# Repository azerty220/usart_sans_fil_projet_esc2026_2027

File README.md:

# Projet de Transmission UART Sans Fil
Projet Système réalisé en troisième année spécialité Electronique et Systèmes de Communication à l'ENSEA : 

> Mise en place d'une communication sans fil USART avec un drône

## Cahier des charges

L'objectif de ce projet est de concevoir une chaîne de transmission/réception RF à partir de composants existants. Cet émetteur-récepteur est destiné à la communication avec un drone. Il y a donc une contrainte de place sur au moins une des versions du système.

Contraintes générales :

    Portée du système : 10m
    Durée du projet : 40h
    Budget : 250€

Paramètres de l'USART fourni : 

    Débit : 115 200 baud
    8 bits de données
    1 bit de parité (pair)
    1 bit de stop

## Choix de la fréquence porteuse et de la modulation
Nous avons choisi une porteuse à **868MHz**, ainsi que la modulation **ASK**,    
- Notre choix s'est porté sur la modulation ASK afin d'obtenir une portée nettement supérieure. De plus, nous avons pris en compte l'expérience d'un groupe ayant réalisé ce même projet en 2025 avec la modulation BPSK : leur choix avait entraîné de lourdes difficultés, notamment au niveau de la démodulation et de la récupération de la porteuse en phase. Cette dernière nécessitait en effet une PLL sans erreur de phase, alors qu'une PLL est initialement conçue pour minimiser les erreurs de fréquence.    
- En ce qui concerne la fréquence, nous avons choisi de réutiliser les composants des années précédentes afin de réduire les coûts. De plus, opter pour la bande des 2,4 GHz très proche de la band Wi-Fi nous aurait exposé à de nombreux signaux parasites, qui auraient été difficiles à filtrer.

## Vue d'ensemble du système émission/réception
Voici une description de notre système. Celui-ci s'organise autour d'une chaîne d'émission (composée du modulateur ASK, du PA et du filtrage) et d'une chaîne de réception (composée du filtrage, du LNA et du démodulateur ASK). Pour permettre l'utilisation d'une seule antenne dans les deux modes, les deux chaînes sont reliées par un Switch RF qui permet de passer d'un mode à l'autre. L'ensemble est piloté par un microcontrôleur µC et la porteuse elle est générée par l'oscillateur local :    

Dans un premier temps, nous avons découpé le système par fonctions : chaque binôme s'est vu assigner une tâche spécifique et devait réaliser un premier PCB (2 couches) dédié. Dans un second temps, une fois les tests validés, un PCB unique à 4 couches a été conçu pour regrouper l'ensemble du système.

# Description de la chaîne d'émission
Le rôle principal de la chaîne d'émission, consiste à traiter les données numériques reçues par liaison UART, à générer une porteuse radiofréquence à 868 MHz (stabilisée par un oscillateur local à boucle à verrouillage de phase (PLL)), puis à appliquer une modulation d'amplitude de type ASK (Amplitude Shift Keying). Le signal ainsi modulé traverse ensuite un étage de filtrage avant d'être acheminé vers l'antenne.
    <br>Le développement de cette chaîne d'émission a été structuré autour de plusieurs objectifs clés :
        <br> 1- Garantir l'intégrité et la fiabilité de la transmission des données numériques via l'interface UART.
        <br> 2- Produire un signal porteur RF stable, propre et paramétrable.
        <br> 3- Exécuter une modulation ASK fidèle aux trames de données à transmettre.
        <br> 4- Filtrer efficacement le signal radiofréquence pour respecter les normes en vigueur avant son émission par l'antenne.
## Bloc génération de la porteuse et modulation ASK
Cette partie décrit le fonctionnement des premiers bloc (Modulateur ASK et Oscillateur Local) de la chaîne détaillée précédemment, la génération de la porteuse sera réalisée par le synthétiseur de fréquence à boucle à verrouillage de phase (PLL) l’ADF4350, afin d’avoir une référence de fréquence, ce dernier sera relié à l’oscillateur ECS-TXD-20CSMV-AC-260-AY-TR et enfin pour réaliser la modulation ASK, nous utiliserons un switch RF, l’ADG918BCPZ.

### 1- interface Nucléo/PCB RF
La communication entre la carte microcontrôleur (Nucleo STM32) et le PCB RF est assurée par plusieurs connecteurs dédiés :

    • Connecteur d'interface SPI (J2) : regroupant les signaux de configuration SCK (horloge de communication), DATA (données de configuration), LE (validation du registre sélectionné) et CE (activation du composant), ainsi que la masse GND, permettant le paramétrage du synthétiseur de fréquence.
    • Connecteur de commande (J3) : acheminant le signal de commande UART_RX issu du microcontrôleur vers le modulateur ASK.
    • Connecteur d'alimentation (J6) : fournissant les tensions +3.3V, +2V5 (utiles pour alimenter l’ADF4350, ADG918 et l’oscillateur) et la référence de masse GND à la carte.
### 2- Génération de la porteuse

###3- Modulation ASK
<br>-> SMA vers le PCB amplificateur de puissance et filtrage
<br> Vue d'ensemble du PCB

## Bloc amplificateur de puissance et filtrage
Callum et Elise

# Switch RF et antenne
Commutation entre les 2 modes -> Johan

# Description de la chaîne de réception
choix des composants modules par module
## Bloc filtrage et LNA
Julie L et Rafik
## Bloc Démodulateur
Awa

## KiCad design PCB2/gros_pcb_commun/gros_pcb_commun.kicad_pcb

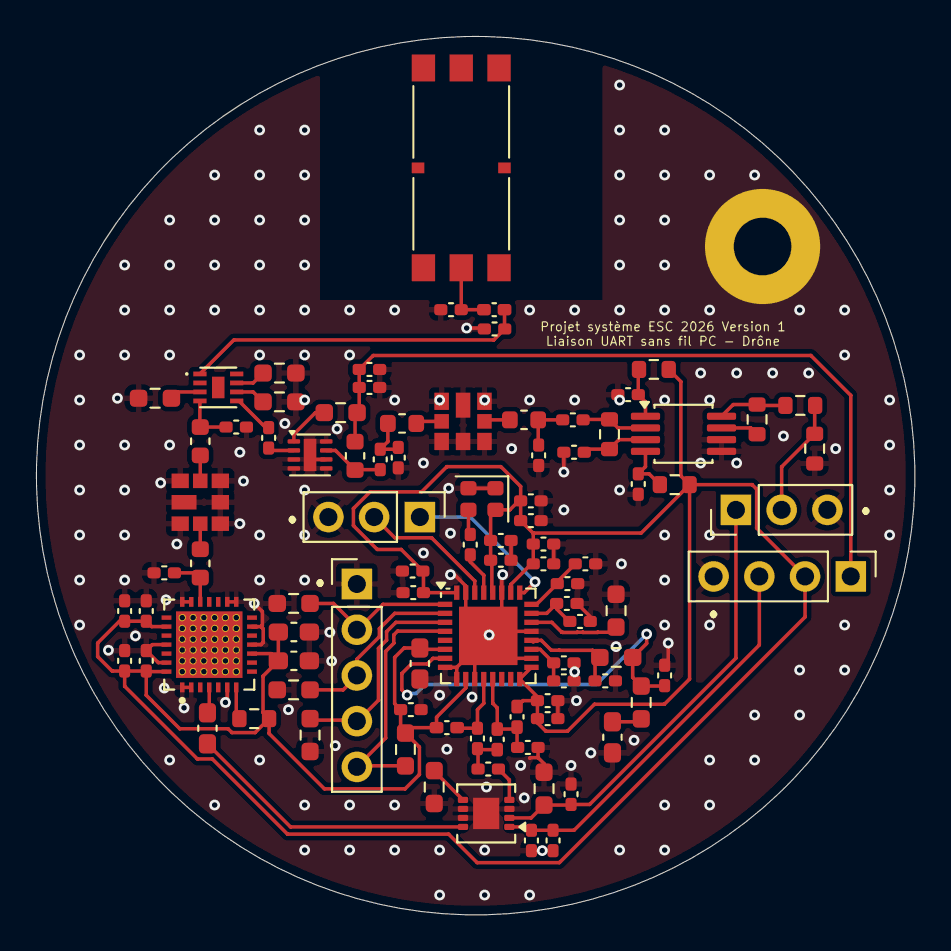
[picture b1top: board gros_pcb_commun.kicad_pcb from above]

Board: 2 copper layers, 48.8 x 48.8 mm, 93 parts (0 on the bottom side), 52 nets.

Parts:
AE1: Antenna; AE_Wurth_WE-MCA_7488910092
C1, C3, C5, C7, C9: 100 nF; C_0402_1005Metric_Pad0.74x0.62mm_HandSolder
C2, C4, C6, C10, C13, C15, C17, C27: 10 pF; C_0402_1005Metric_Pad0.74x0.62mm_HandSolder
C8: 10 pF; C_0603_1608Metric_Pad1.08x0.95mm_HandSolder
C11: 1 uF; C_0402_1005Metric_Pad0.74x0.62mm_HandSolder
C12, C14, C16, C18, C28, C42, C43: 0.1 uF; C_0402_1005Metric_Pad0.74x0.62mm_HandSolder
C19: 1 nF; C_0402_1005Metric_Pad0.74x0.62mm_HandSolder
C20, C21: 4 nF; C_0402_1005Metric_Pad0.74x0.62mm_HandSolder
C22: 120 pF; C_0402_1005Metric_Pad0.74x0.62mm_HandSolder
C23: 42.3 nF; C_0402_1005Metric_Pad0.74x0.62mm_HandSolder
C24: 575 nF; C_0603_1608Metric_Pad1.08x0.95mm_HandSolder
C25: 19.3 nF; C_0402_1005Metric_Pad0.74x0.62mm_HandSolder
C26: 100 pF; C_0402_1005Metric_Pad0.74x0.62mm_HandSolder
C29, C32, C35, C36: 0.1u; C_0402_1005Metric_Pad0.74x0.62mm_HandSolder
C30: 2.7p; C_0402_1005Metric_Pad0.74x0.62mm_HandSolder
C31: 33p; C_0603_1608Metric_Pad1.08x0.95mm_HandSolder
C33, C37: 10u; C_0603_1608Metric_Pad1.08x0.95mm_HandSolder
C34: 3.5p; C_0402_1005Metric_Pad0.74x0.62mm_HandSolder
C38: 3.9pF; C_0402_1005Metric_Pad0.74x0.62mm_HandSolder
C39: 3.3pF; C_0402_1005Metric_Pad0.74x0.62mm_HandSolder
C40, C41: 680 pF; C_0402_1005Metric_Pad0.74x0.62mm_HandSolder
C44: 47pF; C_0402_1005Metric_Pad0.74x0.62mm_HandSolder
C45: 4.7pF; C_0402_1005Metric_Pad0.74x0.62mm_HandSolder
C46: 100nF; C_0402_1005Metric_Pad0.74x0.62mm_HandSolder
C47: 100pF; C_0402_1005Metric_Pad0.74x0.62mm_HandSolder
C48: 2,7pF; C_0402_1005Metric_Pad0.74x0.62mm_HandSolder
C49: 3,5pF; C_0402_1005Metric_Pad0.74x0.62mm_HandSolder
FL1: SF2425E
H3: MountingHole_Pad; MountingHole_3.2mm_M3_Pad
J1: Conn_01x03_Pin; PinHeader_1x03_P2.54mm_Vertical
J2: Conn_01x04_Pin; PinHeader_1x04_P2.54mm_Vertical
J3: Conn_01x05; PinHeader_1x05_P2.54mm_Vertical
J4: Conn_01x03; PinHeader_1x03_P2.54mm_Vertical
L1: 68 nH; L_0402_1005Metric_Pad0.77x0.64mm_HandSolder
L2, L3: 18 nH; L_0402_1005Metric_Pad0.77x0.64mm_HandSolder
L4, L5: 24n; L_0603_1608Metric
L6: 12nH; L_0402_1005Metric_Pad0.77x0.64mm_HandSolder
L7, L8, L9: 22nH; L_0603_1608Metric
R1, R2, R3, R5, R8, R11, R12, R13: 10k; R_0603_1608Metric_Pad0.98x0.95mm_HandSolder
R4: 5.1 k; R_0603_1608Metric_Pad0.98x0.95mm_HandSolder
R6: 59.7; R_0603_1608Metric_Pad0.98x0.95mm_HandSolder
R7: 122; R_0603_1608Metric_Pad0.98x0.95mm_HandSolder
R9: 50; R_0603_1608Metric_Pad0.98x0.95mm_HandSolder
R10: 5k1; R_0603_1608Metric
R14, R17: 10; R_0603_1608Metric
R15: 53,6; R_0603_1608Metric
R16: 0; R_0603_1608Metric
R18: 910; R_0603_1608Metric_Pad0.98x0.95mm_HandSolder
RL1: 1M; R_0603_1608Metric
Rprot1: 500; R_0603_1608Metric
SF1: SF2425E
U1: ADF4350; LFCSP-32-1EP_5x5mm_P0.5mm_EP3.25x3.25mm
U2: ADG918BCPZ; LFCSP-8-1EP_3x3mm_P0.5mm_EP1.45x1.74mm
U3: SKY66185-11; IC_SKY66185-11
U4: SON50P200X200X60-9N160X90
U5: AD8313xRM; MSOP-8_3x3mm_P0.65mm
U6: GRF2070; DFN-8-2x2mm_P0.7mm
Y1: ECS-TXO-20CSMV-AC-260-AY-TR; Oscillator_SMD_SiT_PQFN-4Pin_2.0x1.6mm

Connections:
+2V5: C27.1, C28.1, J2.3, U2.1 (VDD)
+5V: C46.1, C47.1, J2.1, L7.1, R18.1
A+: C20.1, L2.2, U1.12 (RF_OUT_A+)
A-: C21.1, L1.2, L3.2, U1.13 (RF_OUT_A-)
AVDD: C1.2, C2.2, C3.2, C4.2, C5.2, C6.2, C7.2, C8.2, C9.2, C10.2, C11.1, C12.1, C29.2, C32.2, C33.2, C35.1, C36.1, C37.1, J2.2, L1.1, L2.1, R2.1, R10.1, R14.1, R17.2, U1.6 (Vp), U1.10 (AVDD), U1.16 (VVCO), U1.17 (VVCO), U1.26 (PDB_RF), U1.28 (DVDD), U1.32 (SDVDD), U3.10 (VBIAS), U3.23 (VCC3), U3.28 (VCC1), Y1.4 (VDD)
CE: J3.5, R2.2, U1.4 (CE)
DATA: J3.3, R3.1, U1.2 (DATA)
FiltreIN: C30.1, L4.1, U3.19 (RFOUT)
GND: C1.1, C2.1, C3.1, C4.1, C5.1, C6.1, C7.1, C8.1, C9.1, C10.1, C11.2, C12.2, C13.2, C14.2, C15.2, C16.2, C17.2, C18.2, C21.2, C23.2, C24.2, C25.2, C26.2, C27.2, C28.2, C29.1, C30.2, C32.1, C33.1, C34.2, C35.2, C36.2, C37.2, C38.2, C39.2, C41.1, C42.2, C43.1, C46.2, C47.2, C48.2, C49.1, FL1.1 (IN_GND), FL1.3 (GND), FL1.4 (GND), FL1.5 (OUT_GND), FL1.7 (GND), FL1.8 (GND), H3.1, J1.3, J2.4, J3.1, J4.3, R1.2, R3.2, R4.1, R5.2, R8.2, R9.2, R11.2, R12.2, R13.2, RL1.1, SF1.1 (IN_GND), SF1.3 (GND), SF1.4 (GND), SF1.5 (OUT_GND), SF1.7 (GND), SF1.8 (GND), U1.8 (CPGND), U1.9 (AGND), U1.11 (AGNDVCO), U1.18 (AGNDVCO), U1.21 (AGNDVCO), U1.27 (DGND), U1.31 (SDGND), U1.33 (EP), U2.3 (GND), U2.6 (GND), U2.7 (GND), U2.9 (GND), U3.1 (GND), U3.2 (GND), U3.6 (GND), U3.11 (GND), U3.13 (GND), U3.15 (GND), U3.16 (GND), U3.20 (GND), U3.21 (GND), U3.25 (GND), U3.27 (GND), U5.5 (PWDN), U5.6 (COMM), U6.3 (GND), U6.4 (GND), U6.5 (GND), U6.6 (GND), U6.8 (GND), U6.9 (EP), Y1.1 (GROUND_1), Y1.2 (GROUND_2)
LE: J3.4, R1.1, U1.3 (LE)
unnamed: AE1.2 (A), C39.1, L6.2
unnamed: C20.2, C22.1, L3.1
unnamed: C24.1, R6.2
unnamed: C42.1, R14.2, U5.1 (VPOS)
unnamed: C43.2, R17.1, U5.4 (VPOS)
unnamed: C45.2, C48.1, L8.1
unnamed: FL1.2 (IN), L8.2
unnamed: FL1.6 (OUT), L9.1
unnamed: J4.1, U1.25 (LD)
unnamed: J4.2, U1.30 (MUXOUT)
unnamed: L4.2, SF1.2 (IN)
unnamed: L5.1, SF1.6 (OUT)
unnamed: C23.1, R6.1, R7.2, U1.7 (CPout)
unnamed: R4.2, U1.22 (RSET)
unnamed: C25.1, R7.1, U1.20 (VTUNE)
unnamed: R9.1, U2.5 (RF2)
unnamed: C31.2, U3.4 (RFIN)
unnamed: R10.2, U3.7 (~VEN)
unnamed: C38.1, L6.1, U4.1 (RFC)
unnamed: R11.1, U4.3 (V1)
unnamed: R12.1, U4.6 (V2)
unnamed: R13.1, U4.7 (V3)
unnamed: C40.2, R15.1, U5.2 (INHI)
unnamed: C41.2, R15.2, U5.3 (INLO)
unnamed: R16.1, Rprot1.1, U5.8 (VOUT)
unnamed: R16.2, U5.7 (VSET)
unnamed: C44.2, U6.2 (RF_IN)
unnamed: C45.1, L7.2, U6.7 (RF_OUT/VDD)
unnamed: R18.2, U6.1 (VENABLE)
unnamed: C19.1, Y1.3 (OUTPUT)
Porteuse_RFC: C22.2, U2.4 (RFC)
REFIN: C19.2, U1.29 (REFIN)
SCK: J3.2, R5.1, U1.1 (CLK)
TEMP: C13.1, C14.1, U1.19 (TEMP)
VCOM: C15.1, C16.1, U1.23 (VCOM)
VREF: C17.1, C18.1, U1.24 (VREF)
sig0: C26.1, J1.1, R8.1, U2.2 (CTRL)
sig1: C31.1, U2.8 (RF1)
sig2: C34.1, L5.2, U4.4 (RF1)
sig3: C44.1, U4.5 (RF2)
sig4: C40.1, C49.2, L9.2
sig5: J1.2, RL1.2, Rprot1.2

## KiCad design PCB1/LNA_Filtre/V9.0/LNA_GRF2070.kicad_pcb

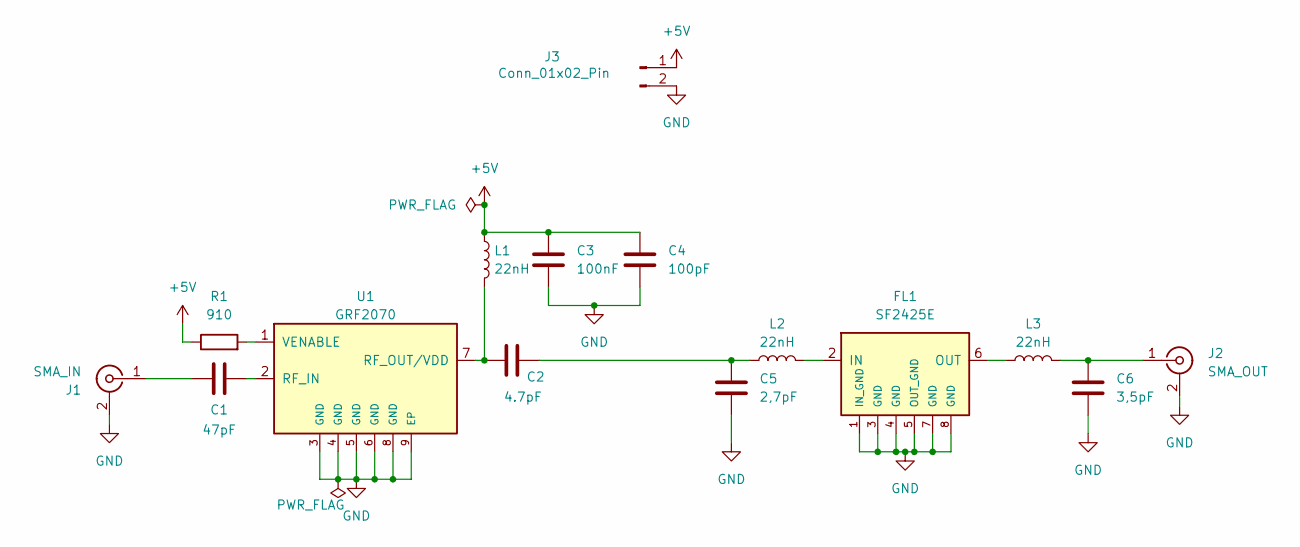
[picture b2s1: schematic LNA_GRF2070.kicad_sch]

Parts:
C1: 47pF; C_0603_1608Metric
C2: 4.7pF; C_0603_1608Metric
C3: 100nF; C_0603_1608Metric
C4: 100pF; C_0603_1608Metric
C5: 2,7pF; C_0603_1608Metric
C6: 3,5pF; C_0603_1608Metric
FL1: SF2425E
J1: SMA_IN; SMA_Samtec_SMA-J-P-H-ST-EM1_EdgeMount
J2: SMA_OUT; SMA_Samtec_SMA-J-P-H-ST-EM1_EdgeMount
J3: Conn_01x02_Pin; PinHeader_1x02_P2.54mm_Vertical
L1, L2, L3: 22nH; L_0603_1608Metric
R1: 910; R_0603_1608Metric_Pad0.98x0.95mm_HandSolder
U1: GRF2070; WDFN-8-1EP_2x2.2mm_P0.5mm_EP0.80x0.54

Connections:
+5V: C3.1, C4.1, J3.1, L1.1, R1.1
GND: C3.2, C4.2, C5.2, C6.1, FL1.1 (IN_GND), FL1.3 (GND), FL1.4 (GND), FL1.5 (OUT_GND), FL1.7 (GND), FL1.8 (GND), J1.2 (Ext), J2.2 (Ext), J3.2, U1.3 (GND), U1.4 (GND), U1.5 (GND), U1.6 (GND), U1.8 (GND), U1.9 (EP)
unnamed: C2.2, C5.1, L2.1
unnamed: FL1.2 (IN), L2.2
unnamed: FL1.6 (OUT), L3.1
unnamed: C1.1, J1.1 (In)
unnamed: C6.2, J2.1 (In), L3.2
unnamed: C1.2, U1.2 (RF_IN)
unnamed: C2.1, L1.2, U1.7 (RF_OUT/VDD)
unnamed: R1.2, U1.1 (VENABLE)

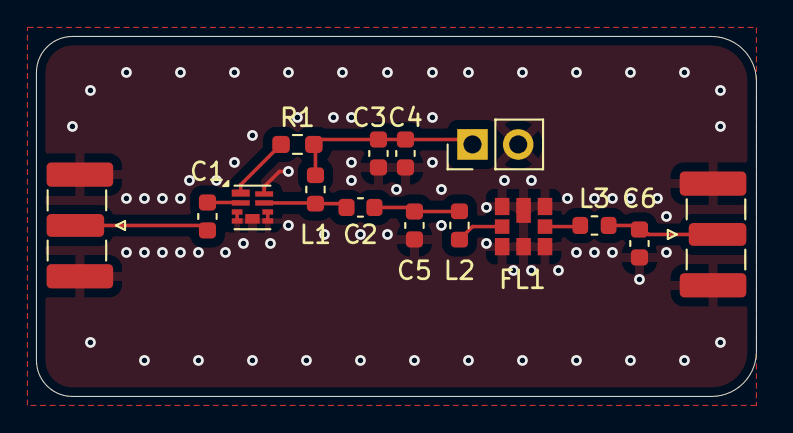
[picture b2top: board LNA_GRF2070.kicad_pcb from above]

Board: 2 copper layers, 40.0 x 20.0 mm, 15 parts (0 on the bottom side), 10 nets.

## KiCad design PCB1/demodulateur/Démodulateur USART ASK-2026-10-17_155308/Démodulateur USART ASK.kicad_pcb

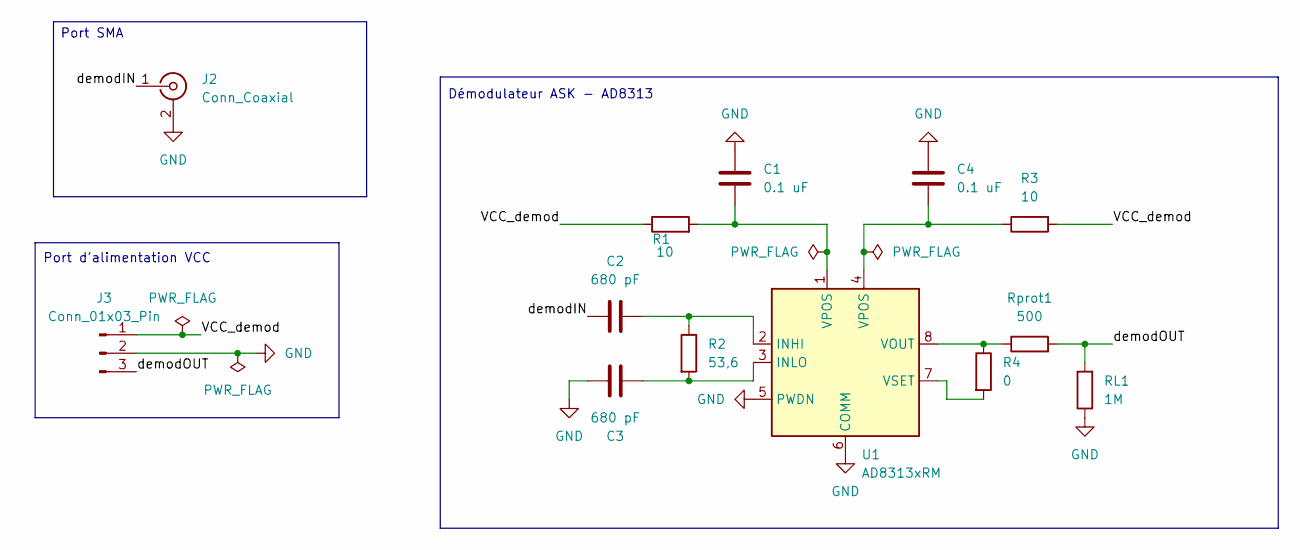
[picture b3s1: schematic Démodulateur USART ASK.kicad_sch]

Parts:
C1, C4: 0.1 uF; C_0603_1608Metric
C2, C3: 680 pF; C_0603_1608Metric
J2: Conn_Coaxial; SMA_Samtec_SMA-J-P-H-ST-EM1_EdgeMount
J3: Conn_01x03_Pin; PinHeader_1x03_P2.54mm_Vertical
R1, R3: 10; R_0603_1608Metric
R2: 53,6; R_0603_1608Metric
R4: 0; R_0603_1608Metric
RL1: 1M; R_0603_1608Metric
Rprot1: 500; R_0603_1608Metric
U1: AD8313xRM; MSOP-8_3x3mm_P0.65mm

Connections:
/VCC_demod: J3.1, R1.1, R3.2
/demodIN: C2.1, J2.1 (In)
/demodOUT: J3.3, RL1.2, Rprot1.2
GND: C1.2, C3.1, C4.1, J2.2 (Ext), J3.2, RL1.1, U1.5 (PWDN), U1.6 (COMM)
unnamed: C1.1, R1.2, U1.1 (VPOS)
unnamed: C4.2, R3.1, U1.4 (VPOS)
unnamed: C2.2, R2.1, U1.2 (INHI)
unnamed: C3.2, R2.2, U1.3 (INLO)
unnamed: R4.1, Rprot1.1, U1.8 (VOUT)
unnamed: R4.2, U1.7 (VSET)

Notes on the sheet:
Démodulateur ASK - AD8313
Port d'alimentation VCC
Port SMA

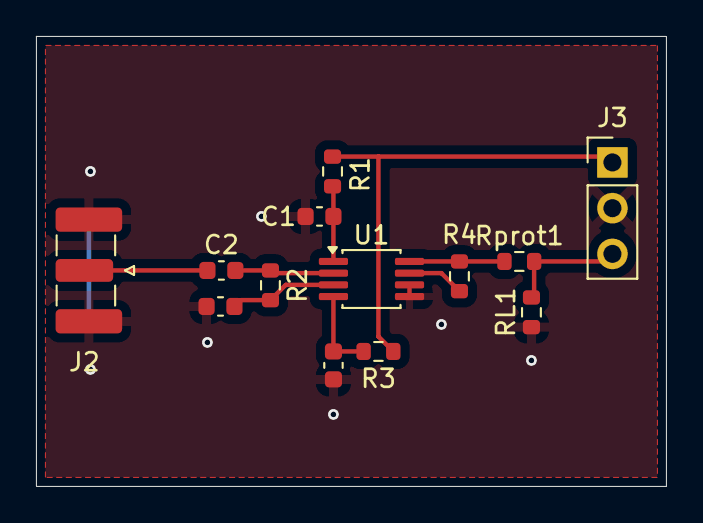
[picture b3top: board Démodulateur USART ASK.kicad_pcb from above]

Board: 2 copper layers, 35.0 x 25.0 mm, 13 parts (0 on the bottom side), 10 nets.

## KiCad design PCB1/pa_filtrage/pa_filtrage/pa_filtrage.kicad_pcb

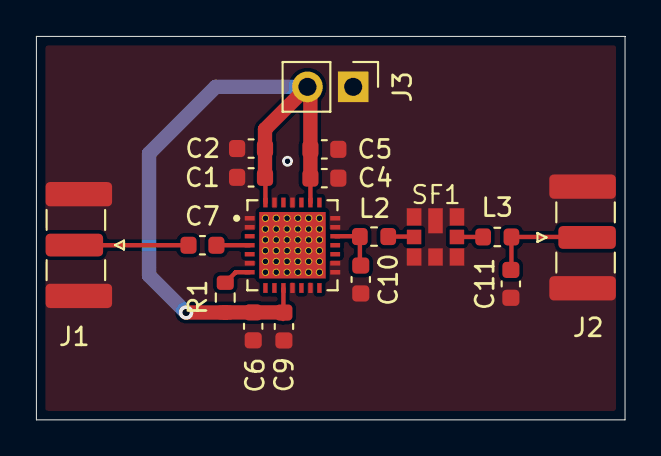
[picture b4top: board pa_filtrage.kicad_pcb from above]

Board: 2 copper layers, 32.7 x 21.3 mm, 17 parts (0 on the bottom side), 9 nets.

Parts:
C1, C4, C6, C9: 0.1u; C_0603_1608Metric
C2, C5: 10u; C_0603_1608Metric
C7: 33p; C_0603_1608Metric
C10: 2.7p; C_0603_1608Metric
C11: 3.5p; C_0603_1608Metric
J1, J2: Conn_Coaxial; SMA_Samtec_SMA-J-P-H-ST-EM1_EdgeMount
J3: Conn_01x02_Pin; PinHeader_1x02_P2.54mm_Vertical
L2, L3: 24n; L_0603_1608Metric
R1: 5k1; R_0603_1608Metric
SF1: SF2425E
U1: SKY66185-11; IC_SKY66185-11

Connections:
+3.3V: C1.2, C2.2, C4.1, C5.1, C6.2, C9.1, J3.2, R1.1, U1.10 (VBIAS), U1.23 (VCC3), U1.28 (VCC1)
FiltreIN: C10.1, L2.1, U1.19 (RFOUT)
FiltreOUT: C11.1, J2.1 (In), L3.2
GND: C1.1, C2.1, C4.2, C5.2, C6.1, C9.2, C10.2, C11.2, J1.2 (Ext), J2.2 (Ext), J3.1, SF1.1 (IN_GND), SF1.3 (GND), SF1.4 (GND), SF1.5 (OUT_GND), SF1.7 (GND), SF1.8 (GND), U1.1 (GND), U1.2 (GND), U1.6 (GND), U1.11 (GND), U1.13 (GND), U1.15 (GND), U1.16 (GND), U1.20 (GND), U1.21 (GND), U1.25 (GND), U1.27 (GND)
unnamed: L2.2, SF1.2 (IN)
unnamed: L3.1, SF1.6 (OUT)
unnamed: C7.2, U1.4 (RFIN)
unnamed: R1.2, U1.7 (~VEN)
RFIN: C7.1, J1.1 (In)

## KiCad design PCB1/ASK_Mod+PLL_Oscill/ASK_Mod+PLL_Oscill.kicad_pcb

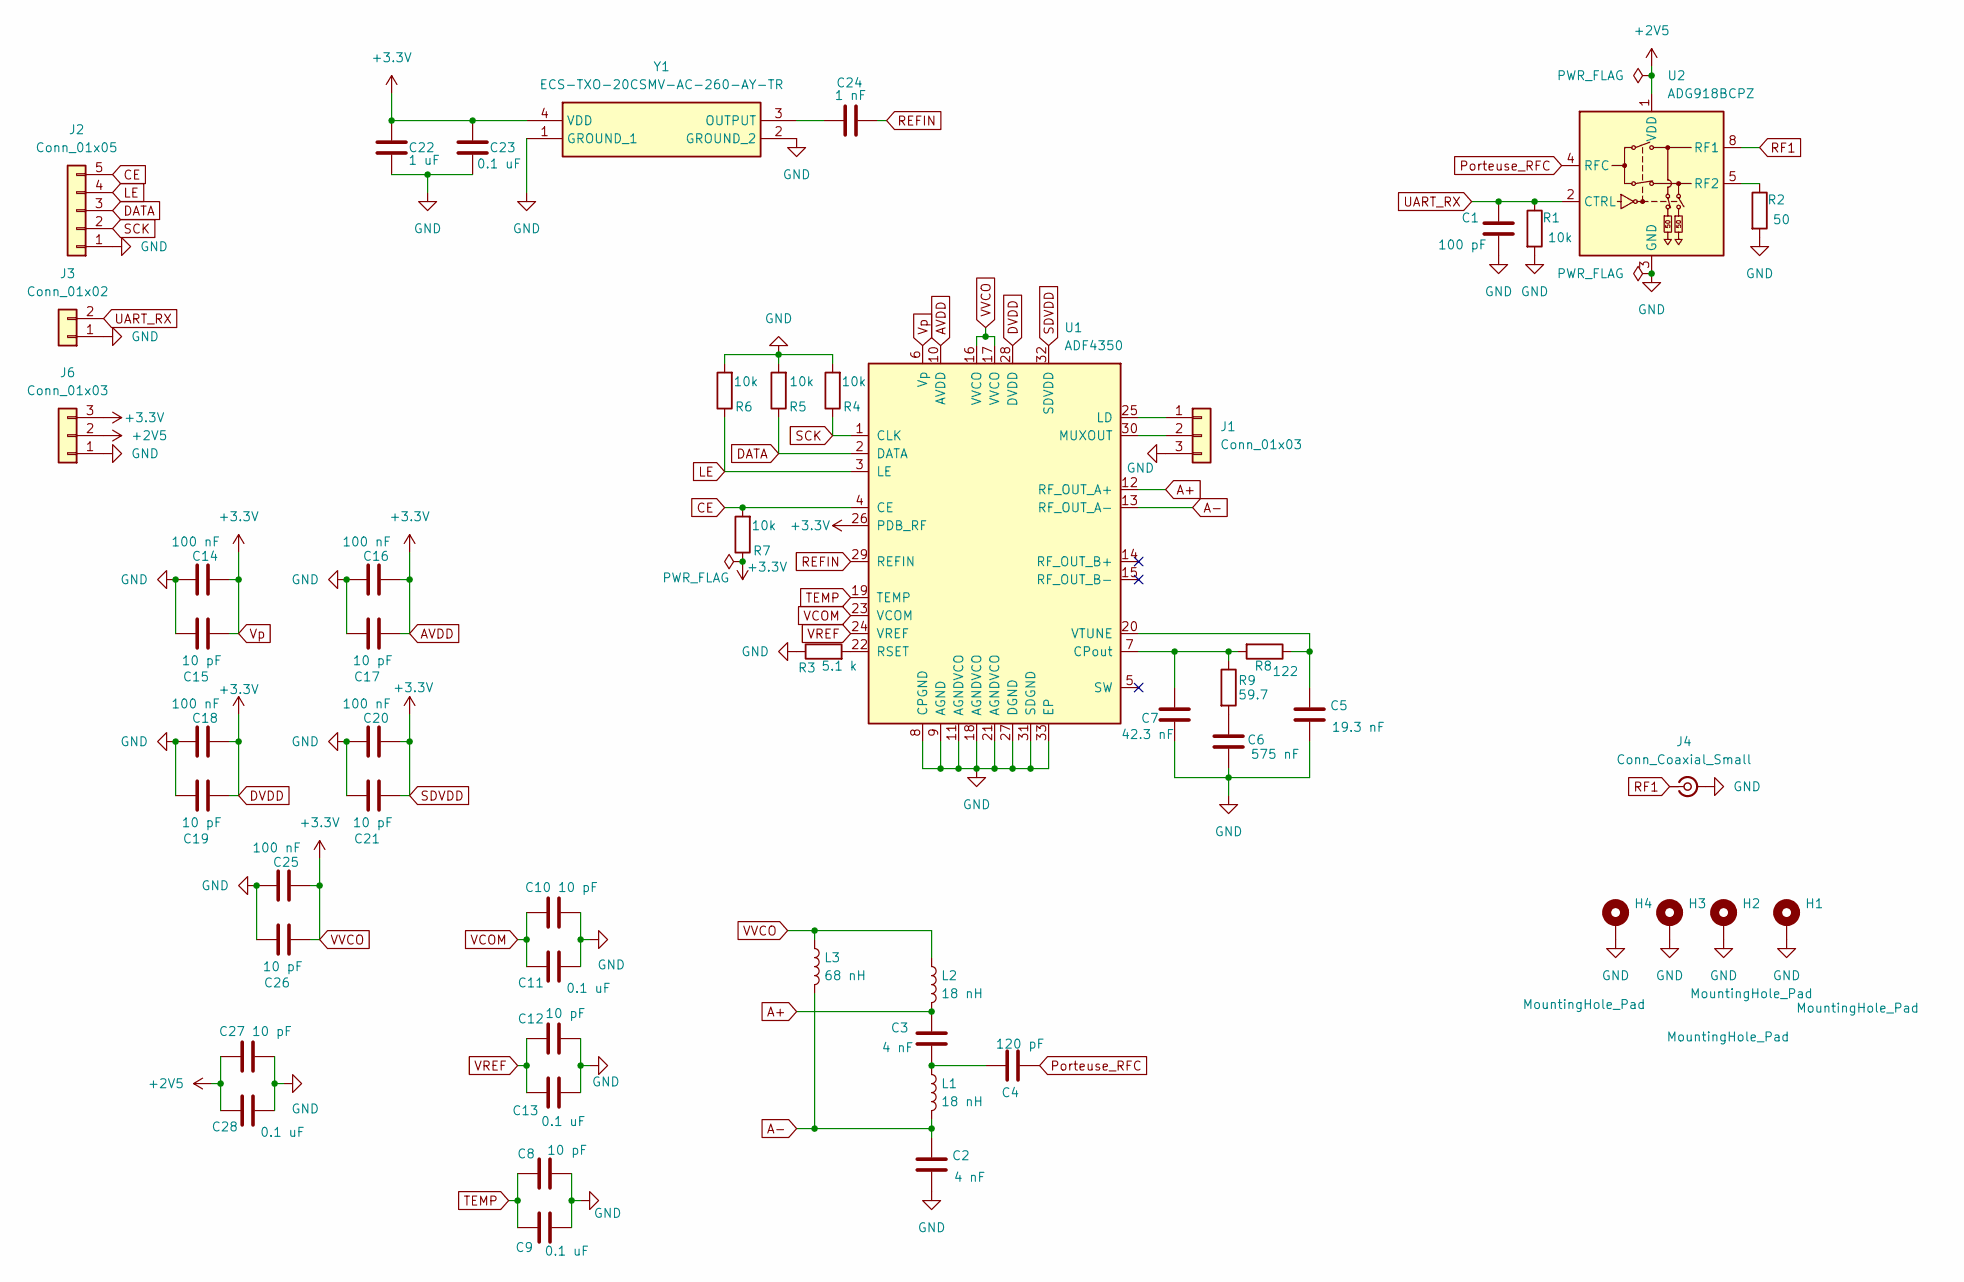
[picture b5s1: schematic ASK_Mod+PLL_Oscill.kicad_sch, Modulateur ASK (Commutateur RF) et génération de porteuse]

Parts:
C1: 100 pF; C_0603_1608Metric_Pad1.08x0.95mm_HandSolder
C2, C3: 4 nF; C_0603_1608Metric_Pad1.08x0.95mm_HandSolder
C4: 120 pF; C_0603_1608Metric_Pad1.08x0.95mm_HandSolder
C5: 19.3 nF; C_0603_1608Metric_Pad1.08x0.95mm_HandSolder
C6: 575 nF; C_0603_1608Metric_Pad1.08x0.95mm_HandSolder
C7: 42.3 nF; C_0603_1608Metric_Pad1.08x0.95mm_HandSolder
C8, C10, C12, C15, C17, C19, C21, C26, C27: 10 pF; C_0603_1608Metric_Pad1.08x0.95mm_HandSolder
C9, C11, C13, C23, C28: 0.1 uF; C_0603_1608Metric_Pad1.08x0.95mm_HandSolder
C14, C16, C18, C20, C25: 100 nF; C_0603_1608Metric_Pad1.08x0.95mm_HandSolder
C22: 1 uF; C_0603_1608Metric_Pad1.08x0.95mm_HandSolder
C24: 1 nF; C_0603_1608Metric_Pad1.08x0.95mm_HandSolder
H1, H2, H3, H4: MountingHole_Pad; MountingHole_3.2mm_M3_Pad
J1, J6: Conn_01x03; PinHeader_1x03_P2.54mm_Vertical
J2: Conn_01x05; PinHeader_1x05_P2.54mm_Vertical
J3: Conn_01x02; PinHeader_1x02_P2.54mm_Vertical
J4: Conn_Coaxial_Small; SMA_Samtec_SMA-J-P-H-ST-EM1_EdgeMount
L1, L2: 18 nH; L_0402_1005Metric_Pad0.77x0.64mm_HandSolder
L3: 68 nH; L_0402_1005Metric_Pad0.77x0.64mm_HandSolder
R1, R4, R5, R6, R7: 10k; R_0603_1608Metric_Pad0.98x0.95mm_HandSolder
R2: 50; R_0603_1608Metric_Pad0.98x0.95mm_HandSolder
R3: 5.1 k; R_0603_1608Metric_Pad0.98x0.95mm_HandSolder
R8: 122; R_0603_1608Metric_Pad0.98x0.95mm_HandSolder
R9: 59.7; R_0603_1608Metric_Pad0.98x0.95mm_HandSolder
U1: ADF4350; LFCSP-32-1EP_5x5mm_P0.5mm_EP3.25x3.25mm
U2: ADG918BCPZ; LFCSP-8-1EP_3x3mm_P0.5mm_EP1.45x1.74mm
Y1: ECS-TXO-20CSMV-AC-260-AY-TR; Oscillator_SMD_SiT_PQFN-4Pin_2.0x1.6mm; Mouser Part Number 520-T20CSMVAC260AYTR

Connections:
+2V5: C27.1, C28.1, J6.2, U2.1 (VDD)
A+: C3.1, L2.2, U1.12 (RF_OUT_A+)
A-: C2.1, L1.2, L3.2, U1.13 (RF_OUT_A-)
AVDD: C14.2, C15.2, C16.2, C17.2, C18.2, C19.2, C20.2, C21.2, C22.1, C23.1, C25.2, C26.2, J6.3, L2.1, L3.1, R7.1, U1.6 (Vp), U1.10 (AVDD), U1.16 (VVCO), U1.17 (VVCO), U1.26 (PDB_RF), U1.28 (DVDD), U1.32 (SDVDD), Y1.4 (VDD)
CE: J2.5, R7.2, U1.4 (CE)
DATA: J2.3, R5.1, U1.2 (DATA)
GND: C1.2, C2.2, C5.2, C6.2, C7.2, C8.2, C9.2, C10.2, C11.2, C12.2, C13.2, C14.1, C15.1, C16.1, C17.1, C18.1, C19.1, C20.1, C21.1, C22.2, C23.2, C25.1, C26.1, C27.2, C28.2, H1.1, H2.1, H3.1, H4.1, J1.3, J2.1, J3.1, J4.2 (Ext), J6.1, R1.2, R2.2, R3.1, R4.2, R5.2, R6.2, U1.8 (CPGND), U1.9 (AGND), U1.11 (AGNDVCO), U1.18 (AGNDVCO), U1.21 (AGNDVCO), U1.27 (DGND), U1.31 (SDGND), U1.33 (EP), U2.3 (GND), U2.6 (GND), U2.7 (GND), U2.9 (GND), Y1.1 (GROUND_1), Y1.2 (GROUND_2)
LE: J2.4, R6.1, U1.3 (LE)
unnamed: C3.2, C4.1, L1.1
unnamed: C6.1, R9.2
unnamed: J1.1, U1.25 (LD)
unnamed: J1.2, U1.30 (MUXOUT)
unnamed: C7.1, R8.2, R9.1, U1.7 (CPout)
unnamed: R3.2, U1.22 (RSET)
unnamed: C5.1, R8.1, U1.20 (VTUNE)
unnamed: R2.1, U2.5 (RF2)
unnamed: C24.1, Y1.3 (OUTPUT)
Porteuse_RFC: C4.2, U2.4 (RFC)
REFIN: C24.2, U1.29 (REFIN)
RF1: J4.1 (In), U2.8 (RF1)
SCK: J2.2, R4.1, U1.1 (CLK)
TEMP: C8.1, C9.1, U1.19 (TEMP)
UART_RX: C1.1, J3.2, R1.1, U2.2 (CTRL)
VCOM: C10.1, C11.1, U1.23 (VCOM)
VREF: C12.1, C13.1, U1.24 (VREF)

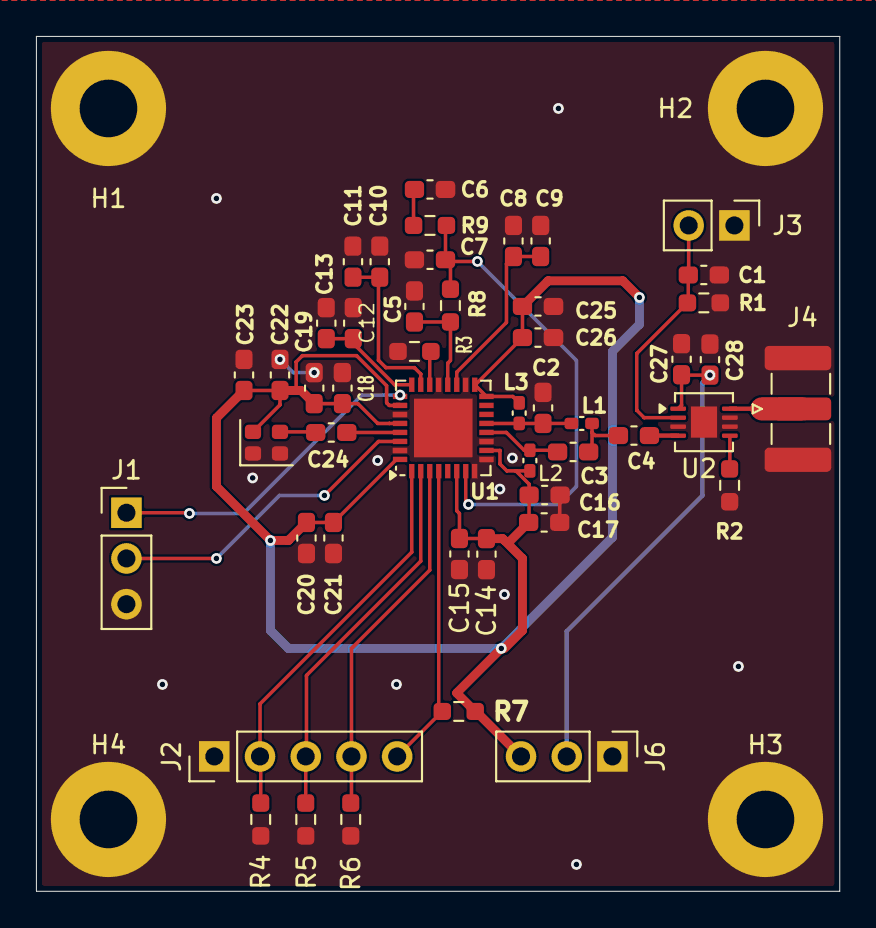
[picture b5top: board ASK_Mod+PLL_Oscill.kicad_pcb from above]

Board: 2 copper layers, 44.6 x 47.5 mm, 52 parts (0 on the bottom side), 25 nets.

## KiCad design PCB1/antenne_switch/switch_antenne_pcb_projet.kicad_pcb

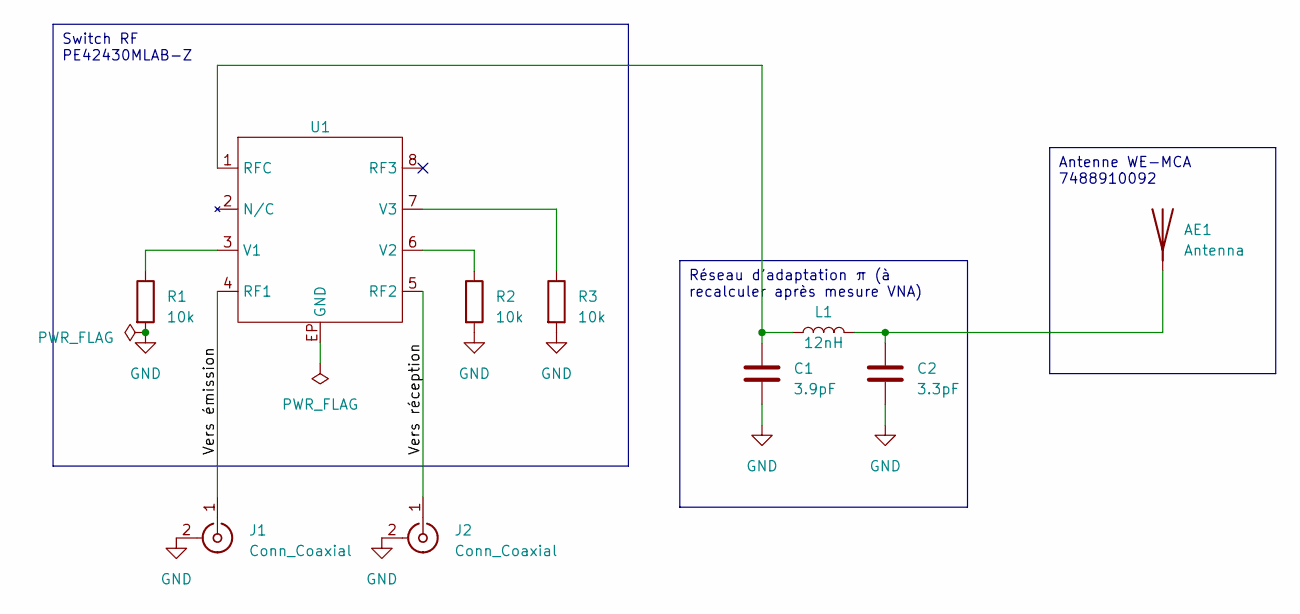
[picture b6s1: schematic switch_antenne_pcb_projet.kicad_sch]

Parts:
AE1: Antenna; AE_Wurth_WE-MCA_7488910092
C1: 3.9pF; C_0402_1005Metric_Pad0.74x0.62mm_HandSolder
C2: 3.3pF; C_0402_1005Metric_Pad0.74x0.62mm_HandSolder
J1, J2: Conn_Coaxial; SMA_Samtec_SMA-J-P-X-ST-EM1_EdgeMount
L1: 12nH; L_0402_1005Metric_Pad0.77x0.64mm_HandSolder
R1, R2, R3: 10k; R_0603_1608Metric_Pad0.98x0.95mm_HandSolder
U1: SON50P200X200X60-9N160X90

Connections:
/Vers réception: J2.1 (In), U1.5 (RF2)
/Vers émission: J1.1 (In), U1.4 (RF1)
GND: C1.2, C2.2, J1.2 (Ext), J2.2 (Ext), R1.2, R2.2, R3.2
unnamed: AE1.2 (A), C2.1, L1.2
unnamed: C1.1, L1.1, U1.1 (RFC)
unnamed: R1.1, U1.3 (V1)
unnamed: R2.1, U1.6 (V2)
unnamed: R3.1, U1.7 (V3)

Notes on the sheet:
Switch RF PE42430MLAB-Z
Réseau d’adaptation π (à recalculer après mesure VNA)
Antenne WE-MCA 7488910092

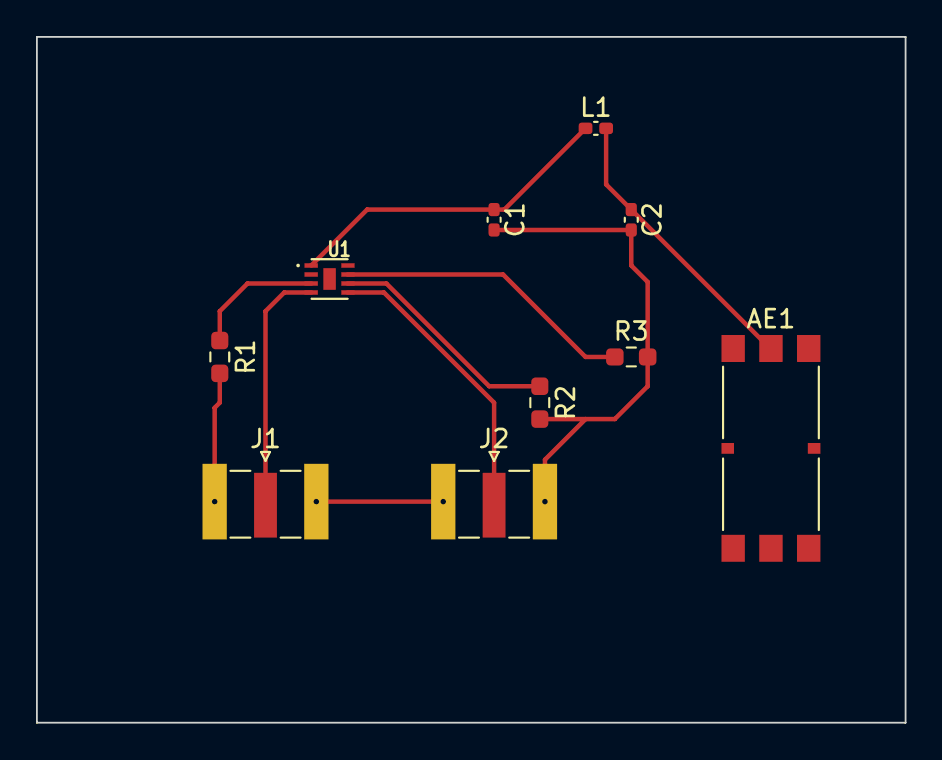
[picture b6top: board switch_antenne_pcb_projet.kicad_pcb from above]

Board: 2 copper layers, 48.3 x 38.1 mm, 10 parts (0 on the bottom side), 8 nets.
